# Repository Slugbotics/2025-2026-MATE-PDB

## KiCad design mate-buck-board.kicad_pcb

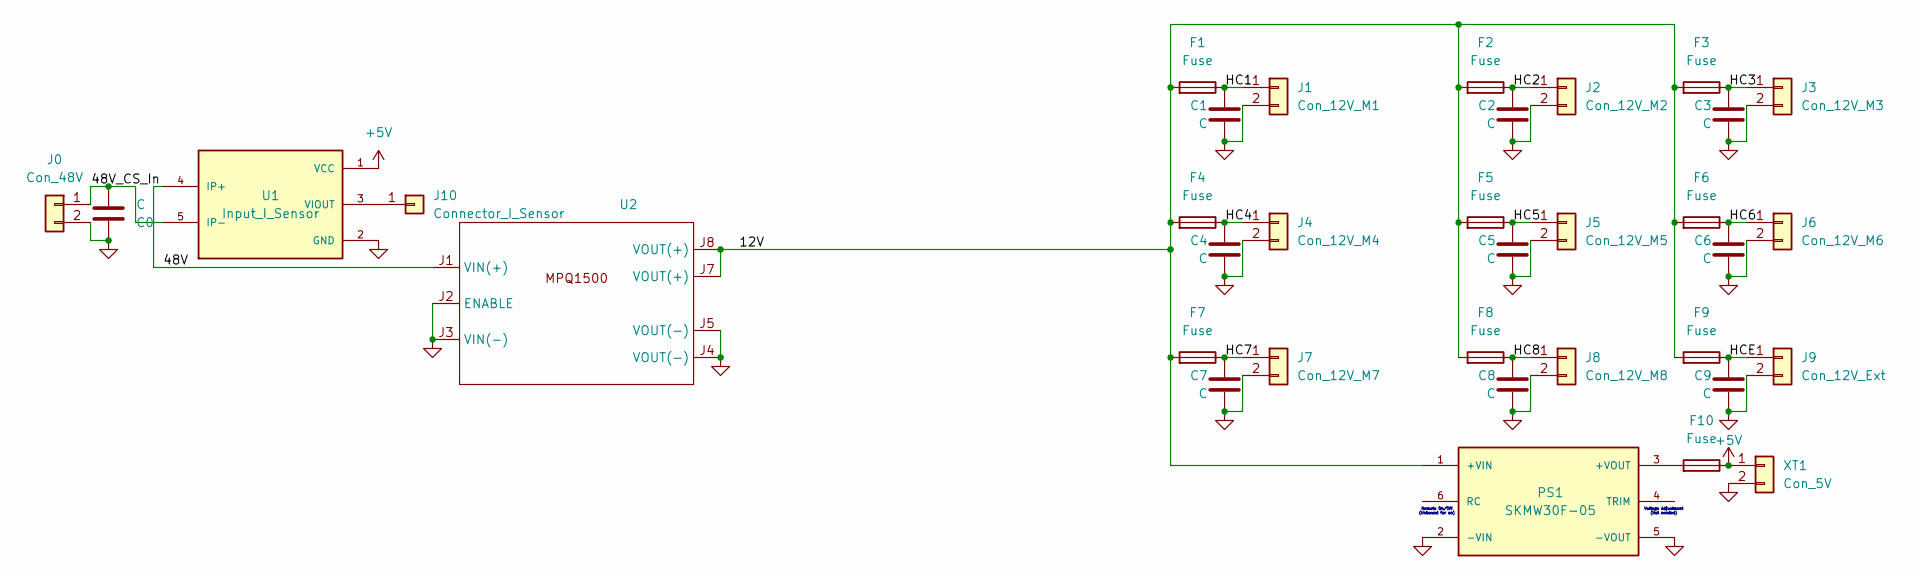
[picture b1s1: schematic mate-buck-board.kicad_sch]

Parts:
C0, C1, C2, C3, C4, C5, C6, C7, C8, C9: C; C_Radial_D8.0mm_H11.5mm_P3.50mm
F1, F2, F3, F4, F5, F6, F7, F8, F9, F10: Fuse; CONN_3557-2_KEY
J0: Con_48V; AMASS_XT60-M_1x02_P7.20mm_Vertical
J1: Con_12V_M1; AMASS_XT60-M_1x02_P7.20mm_Vertical
J2: Con_12V_M2; AMASS_XT60-M_1x02_P7.20mm_Vertical
J3: Con_12V_M3; AMASS_XT60-M_1x02_P7.20mm_Vertical
J4: Con_12V_M4; AMASS_XT60-M_1x02_P7.20mm_Vertical
J5: Con_12V_M5; AMASS_XT60-M_1x02_P7.20mm_Vertical
J6: Con_12V_M6; AMASS_XT60-M_1x02_P7.20mm_Vertical
J7: Con_12V_M7; AMASS_XT60-M_1x02_P7.20mm_Vertical
J8: Con_12V_M8; AMASS_XT60-M_1x02_P7.20mm_Vertical
J9: Con_12V_Ext; AMASS_XT60-M_1x02_P7.20mm_Vertical
J10: Connector_I_Sensor; PinHeader_1x01_P2.54mm_Vertical
PS1: SKMW30F-05; CONV_SKMW30F-05; PARTREV 2022-05-24; DigiKey_Part_Number 1866-4667-ND
U1: Input_I_Sensor; XDCR_ACS772ECB-200U-PFF-T; PARTREV 21
U2: MPQ1500-12V125-L48_Baseplate
XT1: Con_5V; AMASS_XT30UPB-M_1x02_P5.0mm_Vertical

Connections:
+5V: F10.1, U1.1 (VCC), XT1.1
/12V: F1.2, F2.2, F3.2, F4.2, F5.2, F6.2, F7.2, F8.2, F9.2, PS1.1 (+VIN), U2.J7 (VOUT(+)), U2.J8 (VOUT(+))
/48V: U1.4 (IP+), U1.4_1 (IP+), U1.4_2 (IP+), U1.4_3 (IP+), U1.4_4 (IP+), U1.4_5 (IP+), U1.4_6 (IP+), U1.4_7 (IP+), U1.4_8 (IP+), U1.4_9 (IP+), U1.4_10 (IP+), U1.4_11 (IP+), U1.4_12 (IP+), U1.4_13 (IP+), U1.4_14 (IP+), U1.4_15 (IP+), U1.4_16 (IP+), U2.J1 (VIN(+))
/48V_CS_In: C0.1, J0.1, U1.5 (IP-), U1.5_1 (IP-), U1.5_2 (IP-), U1.5_3 (IP-), U1.5_4 (IP-), U1.5_5 (IP-), U1.5_6 (IP-), U1.5_7 (IP-), U1.5_8 (IP-), U1.5_9 (IP-), U1.5_10 (IP-), U1.5_11 (IP-), U1.5_12 (IP-), U1.5_13 (IP-), U1.5_14 (IP-), U1.5_15 (IP-), U1.5_16 (IP-)
/HC1: C1.1, F1.1, J1.1
/HC2: C2.1, F2.1, J2.1
/HC3: C3.1, F3.1, J3.1
/HC4: C4.1, F4.1, J4.1
/HC5: C5.1, F5.1, J5.1
/HC6: C6.1, F6.1, J6.1
/HC7: C7.1, F7.1, J7.1
/HC8: C8.1, F8.1, J8.1
/HCE: C9.1, F9.1, J9.1
GND: C0.2, C1.2, C2.2, C3.2, C4.2, C5.2, C6.2, C7.2, C8.2, C9.2, J0.2, J1.2, J2.2, J3.2, J4.2, J5.2, J6.2, J7.2, J8.2, J9.2, PS1.2 (-VIN), PS1.5 (-VOUT), U1.2 (GND), U2.J2 (ENABLE), U2.J3 (VIN(-)), U2.J4 (VOUT(-)), U2.J5 (VOUT(-)), XT1.2
unnamed: J10.1 (Pin_1_1), U1.3 (VIOUT)
unnamed: F10.2, PS1.3 (+VOUT)

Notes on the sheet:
Voltage Adjustment (Not needed)
Remote On/Off (Unbound for on)

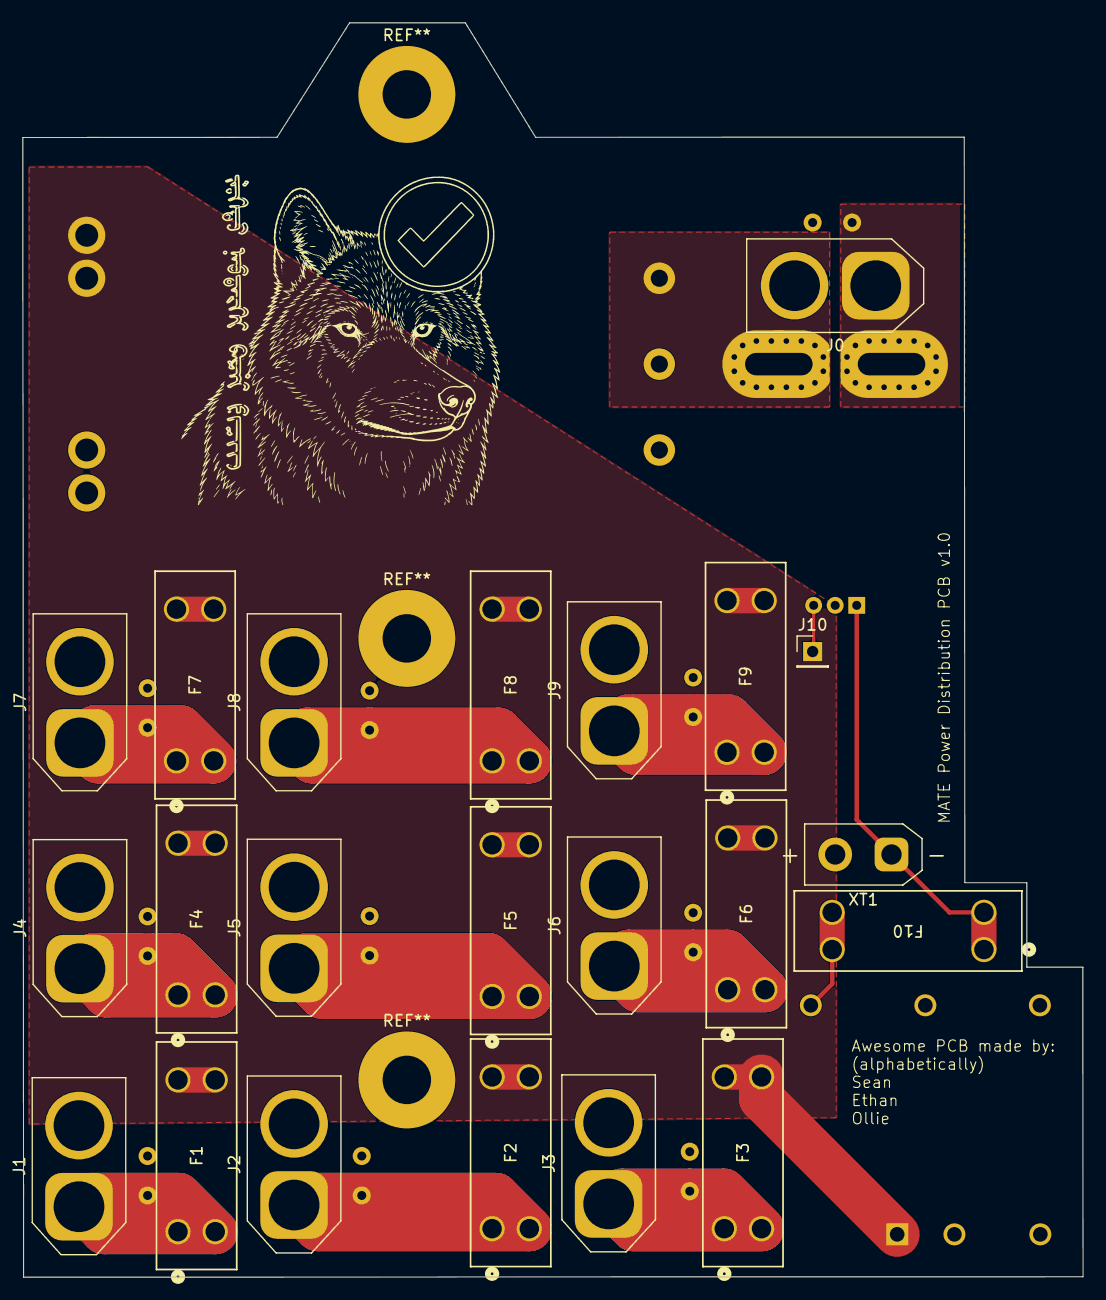
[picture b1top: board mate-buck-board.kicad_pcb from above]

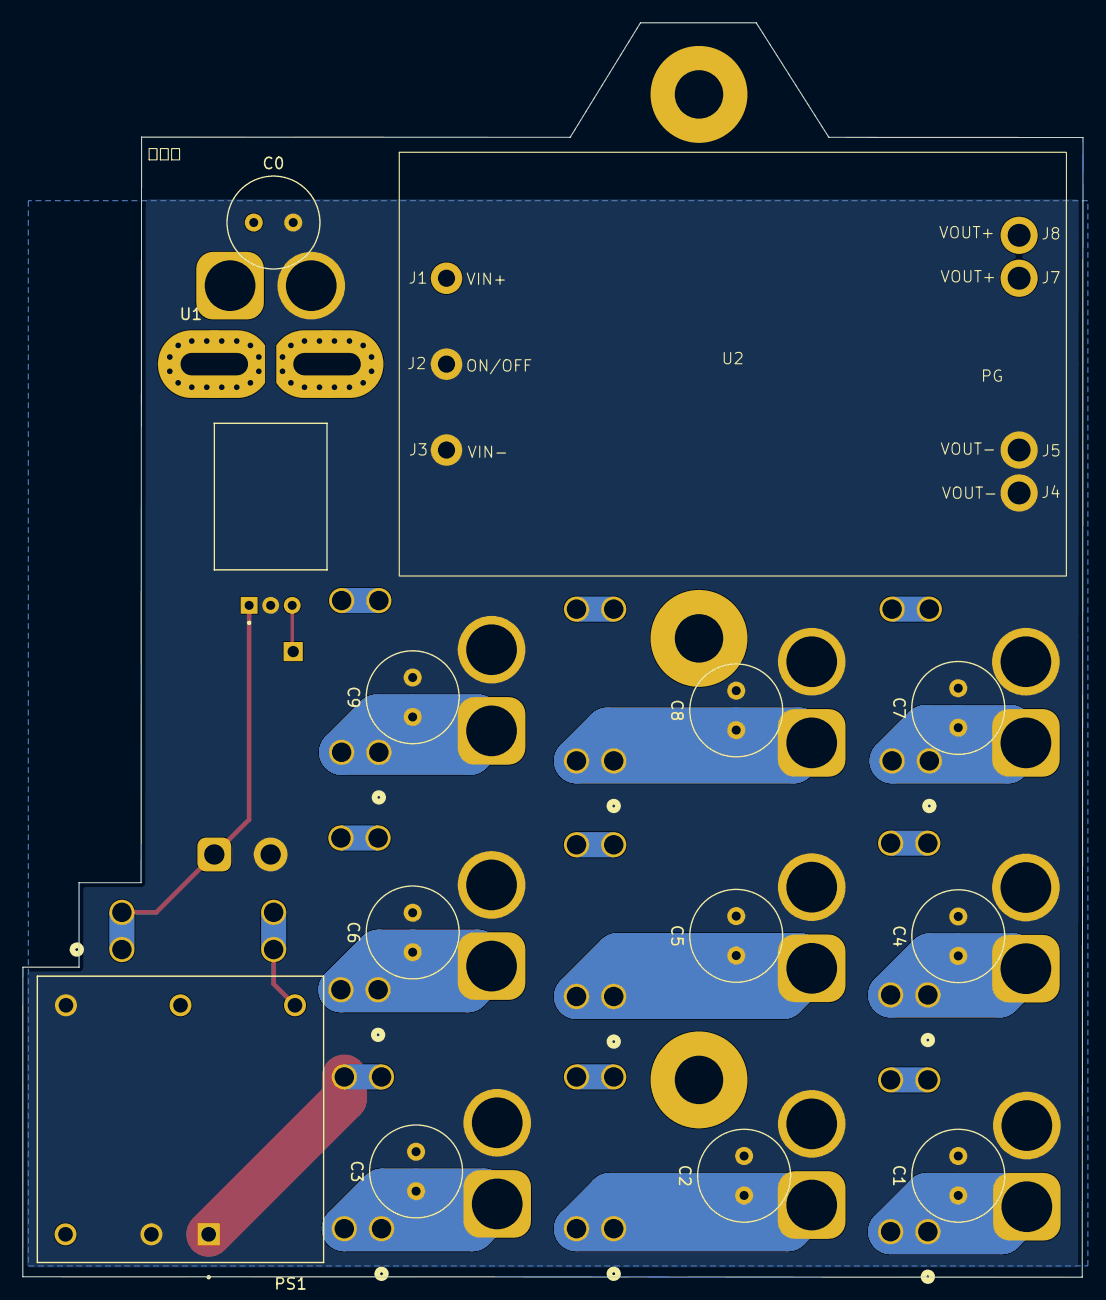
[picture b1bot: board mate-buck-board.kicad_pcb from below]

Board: 2 copper layers, 94.1 x 111.3 mm, 35 parts (13 on the bottom side), 16 nets.

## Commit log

2026-04-24 Initial commit
    added 5v dc-dc
    Minor PCB changes (removed uncessary ground traces); organize schematic
2026-04-24 Changed footprints to reflect the parts we got
2026-04-24 Delete ~mate-buck-board.kicad_pro.lck
    shut up the voices shut up shut up
2026-04-25 Smaller PCB
2026-04-25 Schematic got changed for some reason, committing separately
2026-04-25 Rearranging for mounting
2026-04-25 Revert "Schematic got changed for some reason, committing separately"
    This reverts commit 6daf282efdc33e04f2e097658110ffb19d68f73a.
2026-04-26 Finished probbaly
2026-04-26 Fix holes
2026-04-27 up minimum trace size
2026-04-27 actually save and update minium trace size
